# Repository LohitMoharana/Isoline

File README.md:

<p align="center">
  <b>A heartbeat classifier that sleeps through the flat parts of your ECG.</b><br>
  Two comparators, a few kilobytes of trees, and no ADC streaming in between beats.
</p>

<p align="center">

</p>

---

## 🫀 The idea

An ECG spends most of its time on the flat **isoelectric line**. Isoline does not sample it. Two comparators emit an
*up* or *down* event whenever the signal moves by 0.1 mV, so a quiet baseline produces nothing and the processor sleeps.
Each heartbeat becomes a short burst of events, which a few-kilobyte tree model turns into one of the four AAMI classes:
**N**ormal, **S**upraventricular, **V**entricular or **F**usion.

<br>

| 95.6 % | 5.2 KB | ~90 % | 0.96 |
|:--:|:--:|:--:|:--:|
| accuracy on unseen patients | the tiny classifier | of the time with no events | V-beat F1 |
| <sub>MIT-BIH inter-patient split</sub> | <sub>94.8 % with the AF detector</sub> | <sub>front end and compute stay quiet</sub> | <sub>above a clean re-run of the best published method</sub> |

<br>

## ⚙️ How it works

```mermaid
flowchart LR
    A["ECG<br/>physical mV"] --> B["Analog front end<br/>high-pass · gain · 40 Hz low-pass"]
    B --> C["Two comparators<br/>±0.1 mV level crossing"]
    C -->|sparse up / down events| D["Integer features<br/>event histograms · RR timing<br/>per-patient templates"]
    D --> E["Boosted trees<br/>5.2 KB · integer compares"]
    C -->|beat times| G["AF detector<br/>RR intervals only"]
    G -->|no S labels during AF| E
    E --> F["N · S · V · F"]
```

| Stage | What it does | Why it is cheap |
|---|---|---|
| Level crossing | two comparators and a DAC replace the ADC | about 55 events per second; nothing at all on a flat line |
| Event features | 32-bin up/down histograms around each beat, gain-normalised | counters and shifts |
| Patient adaptation | a running template and four online clusters of *this* patient's beat shapes | about 800 bytes of state, strictly causal |
| Rhythm | RR ratios over short and long memory, plus an RR-only AF/flutter detector | one timer and a few divides per beat |
| Classifier | gradient-boosted trees whose every split is an integer comparison | about 840 compares per beat |

## 📊 Results

All numbers are on **DS2**: 22 patients never seen in training, under the standard de Chazal inter-patient protocol.

<picture>
  <source media="(prefers-color-scheme: dark)" srcset="docs/img/size_vs_accuracy_dark.png">
  
</picture>

| Model | Input | Size | Accuracy | V F1 | S F1 |
|---|---|--:|--:|--:|--:|
| **Isoline, full + AF detector** | comparator events | ~55 KB | **95.64 ± 0.04 %** | **0.956** | 0.32 |
| **Isoline, tiny + AF detector** | comparator events | **5.2 + 5.1 KB** | 94.81 ± 0.04 % | 0.947 | 0.32 |
| Isoline, int8 CNN | comparator events | 9 KB | 93.7 ± 0.4 % | 0.89 | 0.17 |
| RF paper ([Saenz-Cogollo & Agelli 2020](https://doi.org/10.3390/a13040075)), our clean re-run | full-rate ECG | ~300 KB | 95.39 ± 0.09 % | 0.89 | 0.63 |
| LUT / logic-gate networks (2026 preprint) | full-rate ECG | ~16 KB (est.) | 93.6–94.4 % | ≤ 0.91 | 0.01–0.47 |
| Best reported on this split | full-rate ECG | not reported | 96.15 % | 0.94 | 0.69 |

<picture>
  <source media="(prefers-color-scheme: dark)" srcset="docs/img/per_class_dark.png">
  
</picture>

> [!NOTE]
> **Strong on ventricular beats, weak on supraventricular ones.** V beats carry the clearest morphology and need no
> P-wave. S beats that are *not* premature can only be told apart by P-wave shape. Even a full-resolution P-wave
> did not help with the little training data available for them (DS1 has 268 such beats, almost all from two
> patients), so the blind spot is a data limit, not only a front-end one.
> An optional **S-sensitive mode** raises S sensitivity from 22 % to 37 % for 0.6 points of accuracy.
> [Details](docs/EXPERIMENTS.md)

## 🔌 From simulation to silicon

The same model is carried through every stage of the hardware chain. Each stage is measured on DS2 with nothing re-tuned.

| Stage | What runs | DS2 result |
|---|---|---|
| Python front-end model | the reference pipeline (0.05 Hz high-pass, as in the circuit) | 95.51 % full · 94.76 % tiny |
| ngspice circuit | records passed through the simulated analog front end (INA333, servo, gain, Sallen-Key filter) | 95.50 % full · 94.74 % tiny |
| Firmware, virtual hardware-in-the-loop | the **unmodified STM32L432 firmware** (interrupts, DAC thresholds, streaming features, int8 trees) against simulated comparators and DAC | **93.49 % end-to-end**, missed beats counted as errors; beat detection Se 99.69 %, +P 99.08 % |
| Printed circuit board | rev A carrier for a Nucleo-L432KC, 84 × 52 mm, 2 layers, routed and DRC-clean | Gerbers ready; not yet built |

<div align="center">

<br><sub>Rev A, top side. The analog chain runs left to right into the comparators; the Nucleo-32 plugs into the two sockets on the right.</sub>
</div>

<br>

The analog front end draws about **110–170 µW** ([power budget](hardware/POWER_BUDGET.md)). The firmware fits in 66 KB of
flash and 25 KB of RAM on the STM32L432KC, and its features are **bit-exact** with the Python reference.
See [`hardware/`](hardware) for the circuit, simulation and PCB, and [`firmware/`](firmware) for the code.

## 🛡️ Robustness

<table>
<tr>
<td width="56%">
<picture>
  <source media="(prefers-color-scheme: dark)" srcset="docs/img/noise_dark.png">
  
</picture>
</td>
<td>

**Cross-database**, trained once and never tuned:

| Database | Accuracy | V Se |
|---|--:|--:|
| MIT-BIH Supraventricular | 90.3 % | 0.92 |
| European ST-T | 94.8 % | 0.85 |
| MIT-BIH Long-Term | 92.6 % | 0.90 |
| Normal Sinus Rhythm | 99.4 % | – |

Baseline wander is harmless; electrode motion below about 6 dB is the hard case. False alarms on other databases
(4–7 % of normal beats) remain the open problem.

</td>
</tr>
</table>

## 🔬 Method

<picture>
  <source media="(prefers-color-scheme: dark)" srcset="docs/img/journey_dark.png">
  
</picture>

Every configuration was chosen on DS1 or on other databases, then frozen, then evaluated on DS2. Ideas that looked good
in development and failed on unseen patients stay in the record. DS2 has been evaluated **14 times** over the project,
always with frozen configurations. That count is disclosed because it makes any comparison slightly optimistic.
The full lab notebook is [`docs/EXPERIMENTS.md`](docs/EXPERIMENTS.md); the locked configuration (model v1.0) is
described in [`docs/STATUS.md`](docs/STATUS.md).

<details>
<summary><b>Research-integrity rules</b></summary>
<br>

- DS2 is the test set. It is never used for tuning, feature choice, thresholds or early stopping.
- Splits are by **patient**. Extra databases (INCART, SVDB, AFDB, LTDB) are training or development data only.
- Inputs are in physical millivolts with no per-beat normalisation, because real comparators see real volts.
- Features are causal.
- Results are reported as mean ± std over seeds, and negative results are kept.
- Published baselines are re-run under the same protocol before any comparison.
</details>

## 🚀 Reproduce

```bash
pip install -r requirements.txt
python scripts/data/download_data.py --only mitdb svdb                                     # PhysioNet
python -m pytest -q tests                                                                  # feature logic

python scripts/final/final_af_detector.py data/mitdb data/incart data/afdb data/cache results/final   # headline
python scripts/export/export_c.py data/mitdb data/incart data/afdb data/cache                     # C export
python firmware/stm32/sim/hil_run.py data/mitdb DS2 hil.json                               # firmware in the loop
python hardware/kicad/gen/build.py                                                         # board, from netlist to Gerbers
python scripts/figures/make_readme_figures.py                                              # charts
python scripts/figures/make_hero.py --data-dir data/mitdb                                  # banner
```

## 🗂️ Repository

```
isoline/            Python package: front-end model, level crossing, integer features, pipeline
scripts/
  data/             dataset download and synthetic data
  dev/              experiments on DS1 and other databases (never DS2)
  final/            frozen evaluations on DS2 and the shared model code
  export/           C export of the trained model
  figures/          the charts in this README
export/             generated C model (isoline_model.h)
firmware/
  core/             portable C feature and streaming core, bit-exact with Python
  stm32/            STM32L432 application, linker script, Makefile; sim/ holds the virtual HIL
  test/             bit-exactness harnesses
hardware/
  design.py         component values shared by simulation and schematic
  sim/              ngspice front-end simulation
  kicad/            KiCad project; gen/ rebuilds it from design.py
  fab/              Gerbers, drill, BOM, pick-and-place, DRC report
  img/              board renders and schematic
results/
  final/            DS2 results behind every number above
  dev/              development logs
  hardware/         circuit, firmware and HIL results
  archive/          superseded runs
docs/               experiment log, project status, archive
```

## 📄 License

MIT. A research prototype, not a medical device.

<br>

<p align="center"><sub>
Why “Isoline”? The isoelectric line is the flat baseline of an ECG, the part Isoline refuses to spend energy on.
</sub></p>

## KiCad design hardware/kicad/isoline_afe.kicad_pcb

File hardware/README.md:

# Isoline hardware

Status: **design + simulation**. Nothing has been built yet.

## Analog front end (proposal) and its ngspice check

```
electrodes ─► INA333 (G=10, 50 µA) ─► ×30 gain (TLV8541) ─► 40 Hz Sallen-Key LPF (TLV8541) ─► 2 comparators ─► MCU
                 ▲ REF                                                                       (±30 mV steps)
                 └── DC servo integrator (TLV8541, 10 MΩ / 330 nF → 0.05 Hz high-pass)
```

* Total gain 300, so a 0.1 mV input step is **30 mV at the comparators**, which clears the TLV3691's ±17 mV hysteresis.
  At gain 100, a 10 mV step would be swallowed by the hysteresis. This is a design constraint the simulation-only model did not show.
* High-pass at **0.05 Hz**: the algorithm study showed that a 0.5 Hz corner distorts QRS shape and costs accuracy.
* `sim/make_afe_sim.py` writes `sim/afe.cir`, runs ngspice on a real MIT-BIH segment (record 101, with a 100 mV electrode
  offset) and compares the circuit with the Python AFE model used for every accuracy number:

| check | result |
|---|---|
| waveform correlation (input-referred, after 2 s) | **0.993** |
| RMS difference | **25 µV** (a quarter of one 0.1 mV comparator step) |
| level-crossing events, circuit vs model | **433 vs 435 (−0.5 %)** |
| output swing | 0.30 – 1.99 V on a 0–3 V supply (headroom OK) |

* **Known issue:** at power-up the 0.05 Hz servo takes several seconds to cancel electrode offset, and the gain stage
  saturates meanwhile. The simulation starts the servo pre-charged, and the board needs a fast-restore switch (the AD8233
  integrates one). That is a design to-do.
* Op amps are behavioural models (gain, GBW and rail limits from datasheets). Vendor SPICE models should replace them before tape-out.

### Classification accuracy through the simulated circuit

`sim/eval_circuit_accuracy.py` runs all 22 DS2 records through the circuit. ngspice computes the small-signal response
of the netlist and rail clipping is applied (validated against the full transient run: r = 0.99995, 439 vs 433
events). The round-10 system then classifies the result. Models are trained on DS1 + INCART with the Python AFE set to
the circuit's 0.05 Hz high-pass. Nothing is tuned; this is a measurement ([`results/hardware/circuit_accuracy.json`](../results/hardware/circuit_accuracy.json)).

| DS2, 5 seeds | Python AFE model | **ngspice circuit** |
|---|---|---|
| full model + AF detector | 95.51 ± 0.13 % | **95.50 ± 0.11 %** |
| tiny 5.2 KB + AF detector | 94.76 ± 0.11 % | **94.74 ± 0.06 %** |
| idle sparsity | 89.6 % | 89.6 % |
| output clipping | – | 0 % |

Not yet modelled: comparator offset and hysteresis, electrode noise, and beat detection from events (all accuracy
numbers here use annotated R-peak positions, as is standard on this benchmark).

See [POWER_BUDGET.md](POWER_BUDGET.md) for the power analysis and the architecture decision it raises.

## KiCad schematic

`kicad/isoline_afe.kicad_sch` is a native schematic generated by `kicad/gen/make_schematic.py` from the same circuit
description. Every pin has a wire stub and a net label, grouped in six titled blocks. **Validated:** KiCad exports a
netlist from this schematic that is identical, net for net, to the generated netlist (31 nets). Open `isoline_afe.kicad_pro`,
tidy the placement if you like, then *Tools → Update PCB from Schematic*. KiCad 8/9 will upgrade the KiCad-7-format file
on save.

## KiCad: board netlist (generated from the same `design.py` as the simulation)

`kicad/gen/make_netlist.py` → `kicad/isoline_afe.net` (56 parts, 31 nets, all footprints from the standard KiCad
libraries) and `fab/bom.csv`. The board is a **carrier for a NUCLEO-L432KC** (Cortex-M4F with an on-board
ST-LINK), so there is no QFN to hand-solder and no separate programmer to buy.

**Board:** a placed and routed layout is in `kicad/isoline_afe.kicad_pcb` (see *PCB* below). To start over from the
netlist instead: KiCad PCB Editor → *File → Import → Netlist…* → `isoline_afe.net` → *Update PCB*.

| Block | Parts | Notes |
|---|---|---|
| Power | JST-PH 2-pin (BT1) to an external 2×AAA pack with switch, JP1 power select | JP1 1-2 = battery, 2-3 = Nucleo 3V3 from USB (development) |
| Reference | 2×1 MΩ divider + TLV8542 (U4B) buffer | VREF = VCC/2 |
| Input | J1 electrodes (RA−, LL+, RL), 10 k series, 10 MΩ bias to VREF | RL to VREF through 10 k |
| HIL input | J2 + 1 µF + 100 k / 100 Ω attenuator (~1/1000), JP2/JP3 | fit JP2 + JP3 **only** when injecting MIT-BIH from a DAC/audio out |
| In-amp | INA333 (U1), RG = 11.1 k (0.1 %) → G = 10 | pinout checked: RG 1/8, IN− 2, IN+ 3, V− 4, REF 5, OUT 6, V+ 7 |
| Servo / fast restore | TLV8542 U2A integrator 10 MΩ / 330 nF; SN74LVC1G66 (U3) switch + 100 k | MCU D6 (PB1) high for ~1 s at power-up |
| Gain + LPF | U2B ×30; U4A Sallen-Key 40 Hz (100 k, 100 k, 56 n, 27 n) | total gain 300 |
| Comparators | 2 × TLV3691 (U5, U6; SC70-5): UP = AFE > TH_UP, DN = AFE < TH_DN | thresholds from DAC PA4 (A3) / PA5 (A4); events to D2 (PA12) / D3 (PB0) |
| Debug | AFE_OUT → A0 (PA0) through 1 k; 8 test points | |

**Nucleo jumper note.** On the Nucleo-32, A4/A5 share pins with D4/D5 through solder bridges, so PA5 is input-only by
default. Open the relevant bridges (SB16/SB18 per UM1956) before using PA5 as DAC output, and check the exact bridge
numbers for your board revision in UM1956.

### Layout guidance (for you in KiCad)

1. **Two zones:** analog (J1, input resistors, U1, U2, U3, U4) on one side, Nucleo headers and comparators on the other.
   Use one solid ground pour on the bottom layer and do not split it.
2. **Keep high-impedance nodes tiny:** the servo node (SERVO_IN: 10 MΩ + 330 nF) and the 10 MΩ bias resistors. Use short
   traces, no vias if possible, and keep them away from the comparator outputs and the Nucleo. Consider a guard ring tied to VREF.
3. **Symmetric input routing** from J1 to U1 pins 2/3 (equal length, side by side) for CMRR.
4. **One 100 nF decoupling capacitor per IC**, placed right at its V+ pin. Put the 10 µF bulk capacitor near JP1.
5. **Comparators next to the Nucleo header**, so the fast-edged EV_UP / EV_DN traces stay short and far from the analog zone.
6. The 330 nF servo capacitor should be a low-leakage film or C0G/X7R part (leakage sets the corner frequency).
7. Header spacing: CN3 to CN4 = 15.24 mm (600 mil). Pin 1 of both is at the end **away from** the Nucleo's USB connector; with USB pointing up (top view), CN4 (VIN…A0…D13) is the left column and CN3 (D1…D12) the right one. `make_pcb.py` checks this against KiCad's `Module:Arduino_Nano` footprint.

## PCB (rev A): placed, routed, DRC-clean

| Top | Bottom (mirrored) |
|---|---|
|  |  |

- **Board:** 84 × 52 mm, 2 layers, 1.6 mm. All SMD parts are 0805 / SOIC / VSSOP / SC-70 on the top side, with hand-soldering SC-70 pads.
- **Mechanical:** four M3 holes. The Nucleo-32 plugs into two 1×15 sockets with its USB at the top edge. Nothing is placed between the socket rows: the comparators (U5, U6) sit in their own strip just left of J4, so they can be probed and reworked with the Nucleo plugged in, and the board still works if the Nucleo is soldered flat.
- **Rules:** the fab's flat-offer profile: track 0.25 mm, clearance 0.25 mm, vias 0.9 / 0.5 mm, smallest hole 0.5 mm, 1.6 mm FR-4, one rectangular outline. The 0.65 mm-pitch parts (U1 VSSOP-8; U3, U5, U6 SC-70) have their pads trimmed to 0.39 mm wide, so the gaps are 0.26 mm while staying within TI's land pattern for 0.25–0.38 mm leads. An independent geometry check gives a smallest different-net copper gap of 0.260 mm; the drills are 0.50 / 0.75 / 1.00 / 3.20 mm.
- **Ground:** the bottom layer is a near-solid GND plane (only short cross-unders), with a GND pour on top. Every SMD GND pad has its own stitching via, plus a 5 mm lattice of stitching vias.
- **Power:** 2×AAA pack off-board on a JST-PH connector (BT1; 1 = +, 2 = −) instead of the earlier Keystone holder. Its through-hole contacts and pegs collided with the analog section and the sockets.
- **How it was made (reproducible):**
  - `kicad/gen/make_pcb.py` places the parts from `isoline_afe.net` and checks the socket orientation.
  - `kicad/gen/route_grid.py` routes it with a small A* grid router written for this board: exact copper-geometry clearances, F.Cu preferred, GND fan-out first.
  - `kicad/gen/render_pcb.py` draws the pictures.
  - KiCad 7's own DRC (`fab/drc_report.txt`) reports **0 unconnected pads and 0 clearance / hole / silkscreen / courtyard violations**. The 60 remaining "library not configured" warnings only mean the build machine had no footprint library table.
- **Fabrication files:** `fab/isoline_afe_gerbers.zip` (Gerbers + Excellon drill, upload as is), `fab/isoline_afe-pos.csv` (pick-and-place), `fab/bom.csv`.

**Honest layout review (optional hand clean-up in KiCad before ordering):**
- **Electrode traces:** E_POS / E_NEG run 30–42 mm because they also reach the HIL jumpers and attenuator at the lower left. Fine at ECG frequencies, but shorter is better against mains pickup.
- **AFE_OUT** fans out to the comparators, C11, R18 and TP4 over about 70 mm with 10 vias. It is a low-impedance op-amp output, so this is harmless but untidy.
- **Servo node:** SERVO_IN (10 MΩ / 330 nF) is short (16.5 mm) with no vias. A VREF guard ring around it would further reduce leakage, but it is not drawn.
- **Decoupling:** capacitors sit 3–5 mm from their ICs rather than at the V+ pin. At these bandwidths (TLV8542 GBW 8 kHz) with a solid ground plane this is acceptable.

### Before ordering a PCB: checklist

- [ ] Re-check every footprint against the exact ordered part (package suffix: INA333AIDGK, TLV8542ID, TLV3691IDCK, SN74LVC1G66DCK).
- [ ] Confirm the Nucleo-32 header order and solder bridges in UM1956 for your board revision. Physically: hold your Nucleo with USB up, components facing you; the column with VIN/A0/D13 must land on J4 (left).
- [ ] Open the Nucleo solder bridges that tie A4/A5 to D4/D5 (SB16/SB18 per UM1956) so PA5 can drive TH_DN.
- [ ] Check the polarity of your 2×AAA pack's JST-PH lead (red to pin 1 "+"). JST lead colours are not standardised.
- [ ] Open `kicad/isoline_afe.kicad_pcb` in your KiCad, run *Inspect → Design Rules Checker* with your library table, and look at the 3D view.
- [ ] Replace the behavioural op-amp models with TI's SPICE models and re-run `sim/make_afe_sim.py`.
- [ ] Simulate the fast-restore start-up (switch on 1 s, then off).

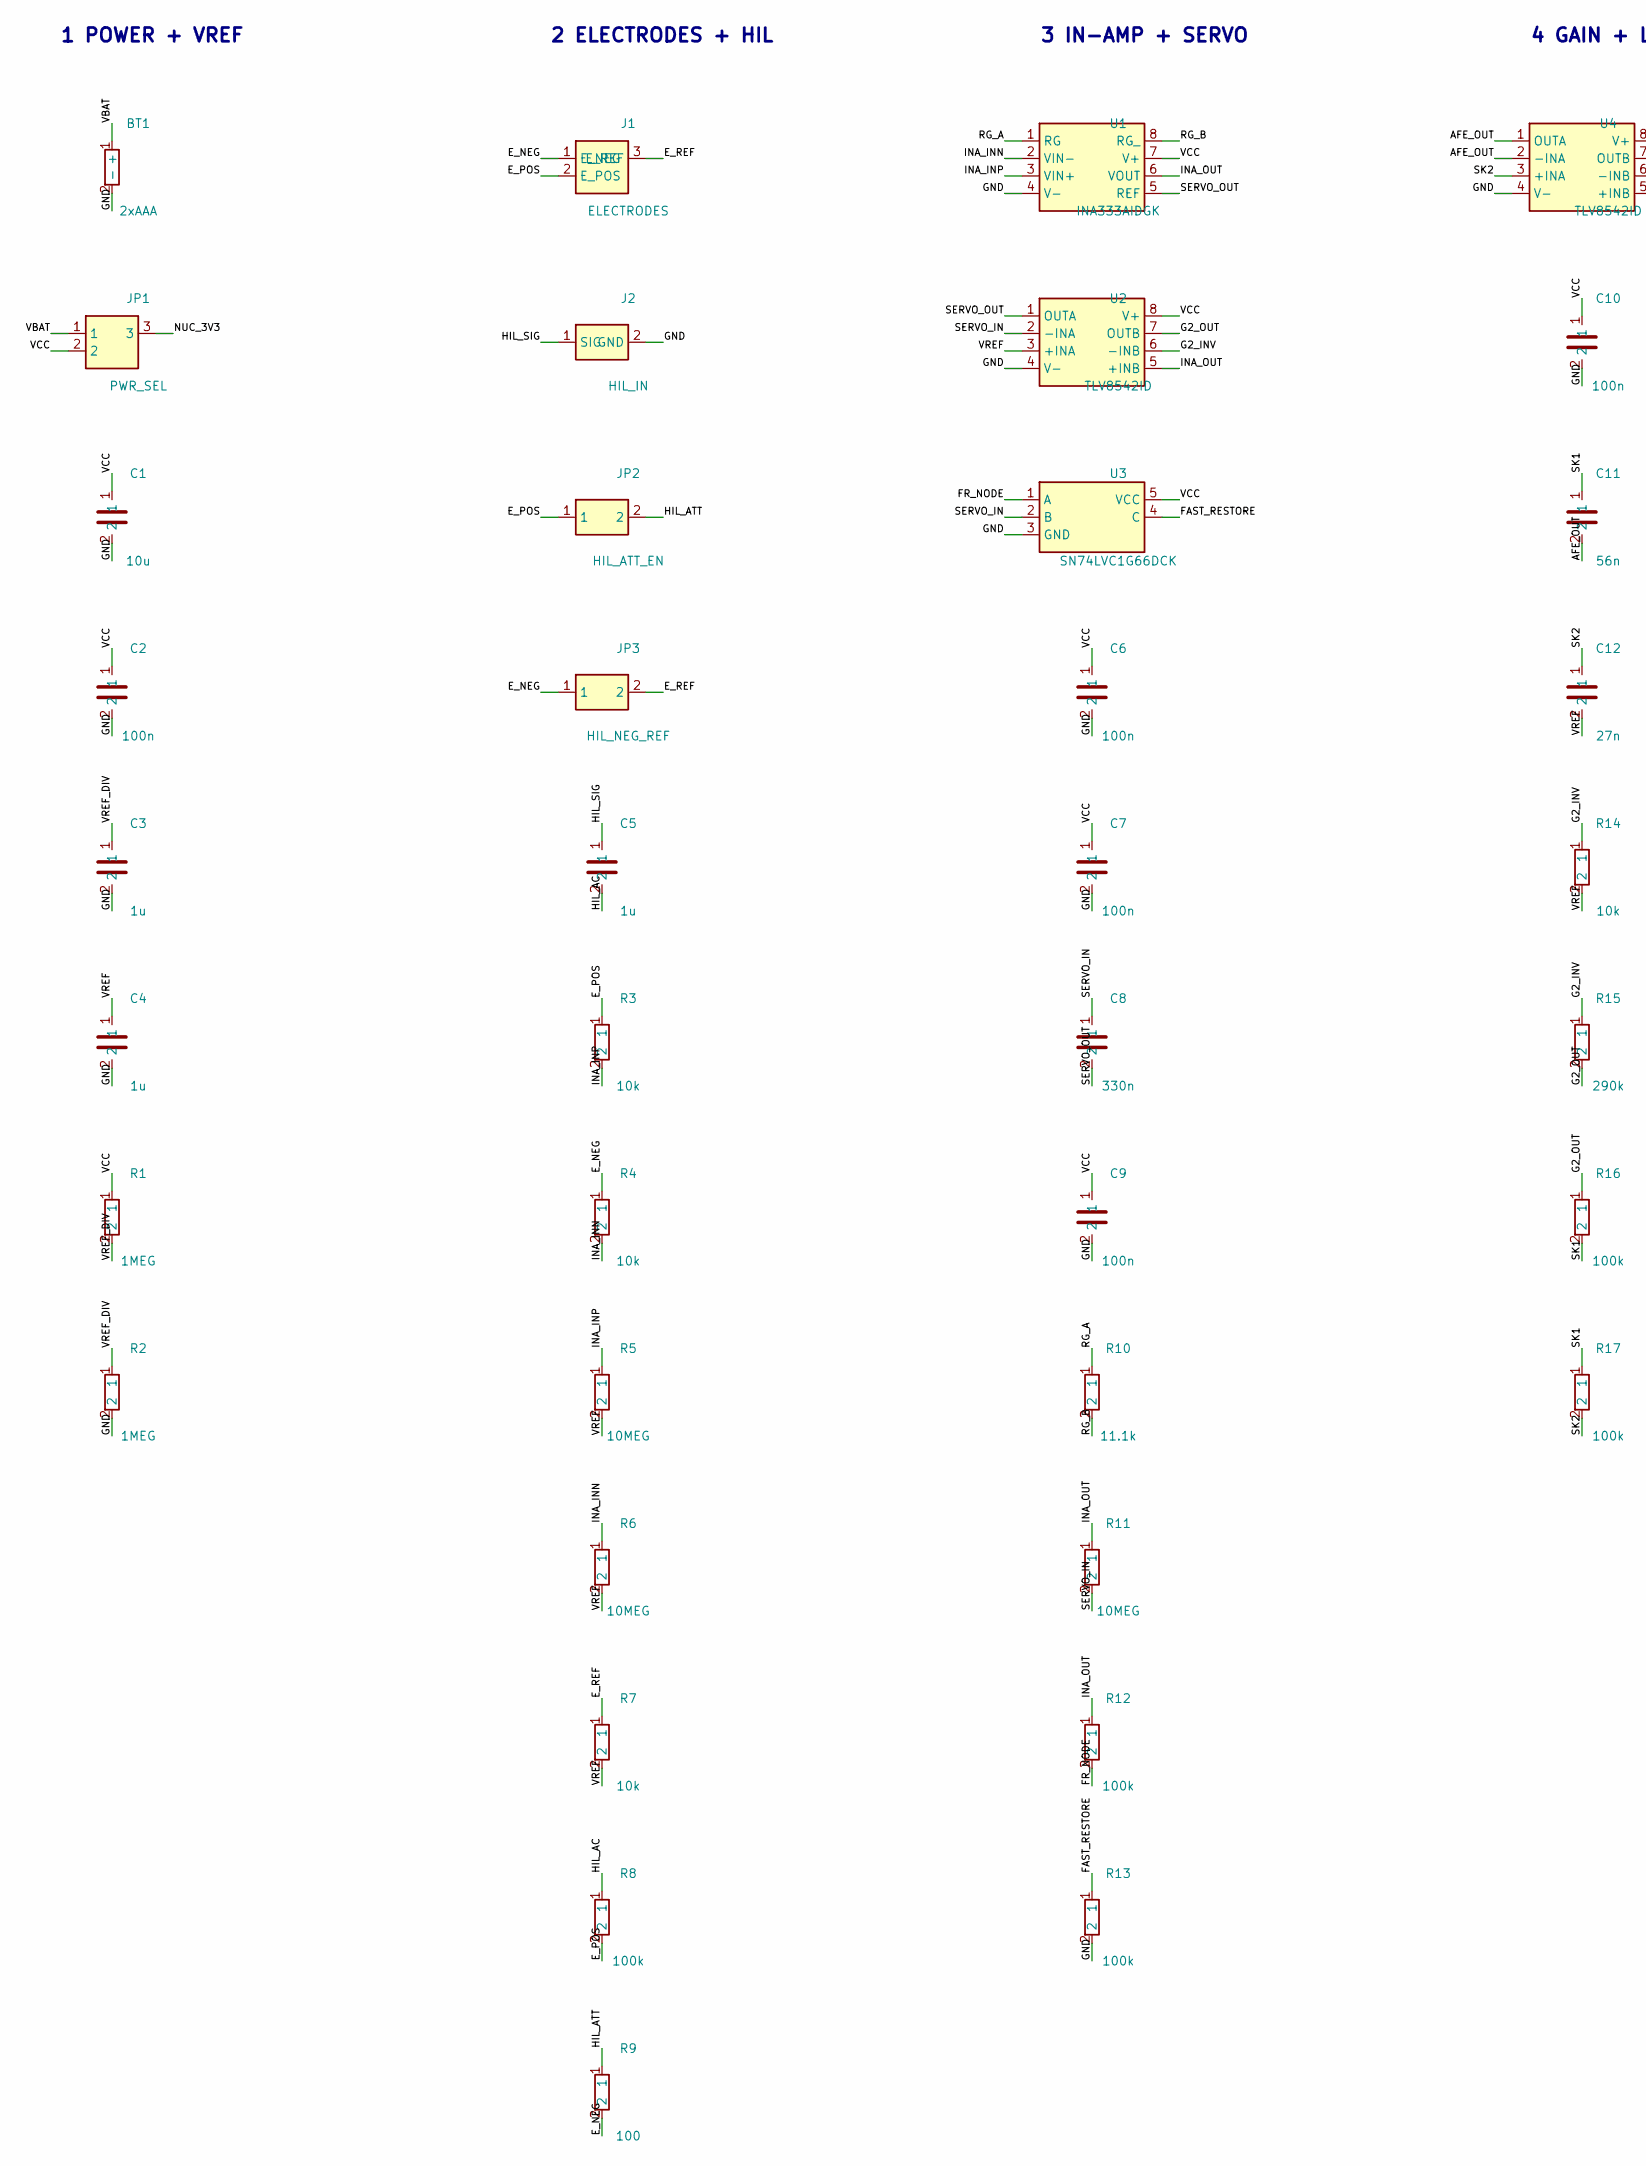
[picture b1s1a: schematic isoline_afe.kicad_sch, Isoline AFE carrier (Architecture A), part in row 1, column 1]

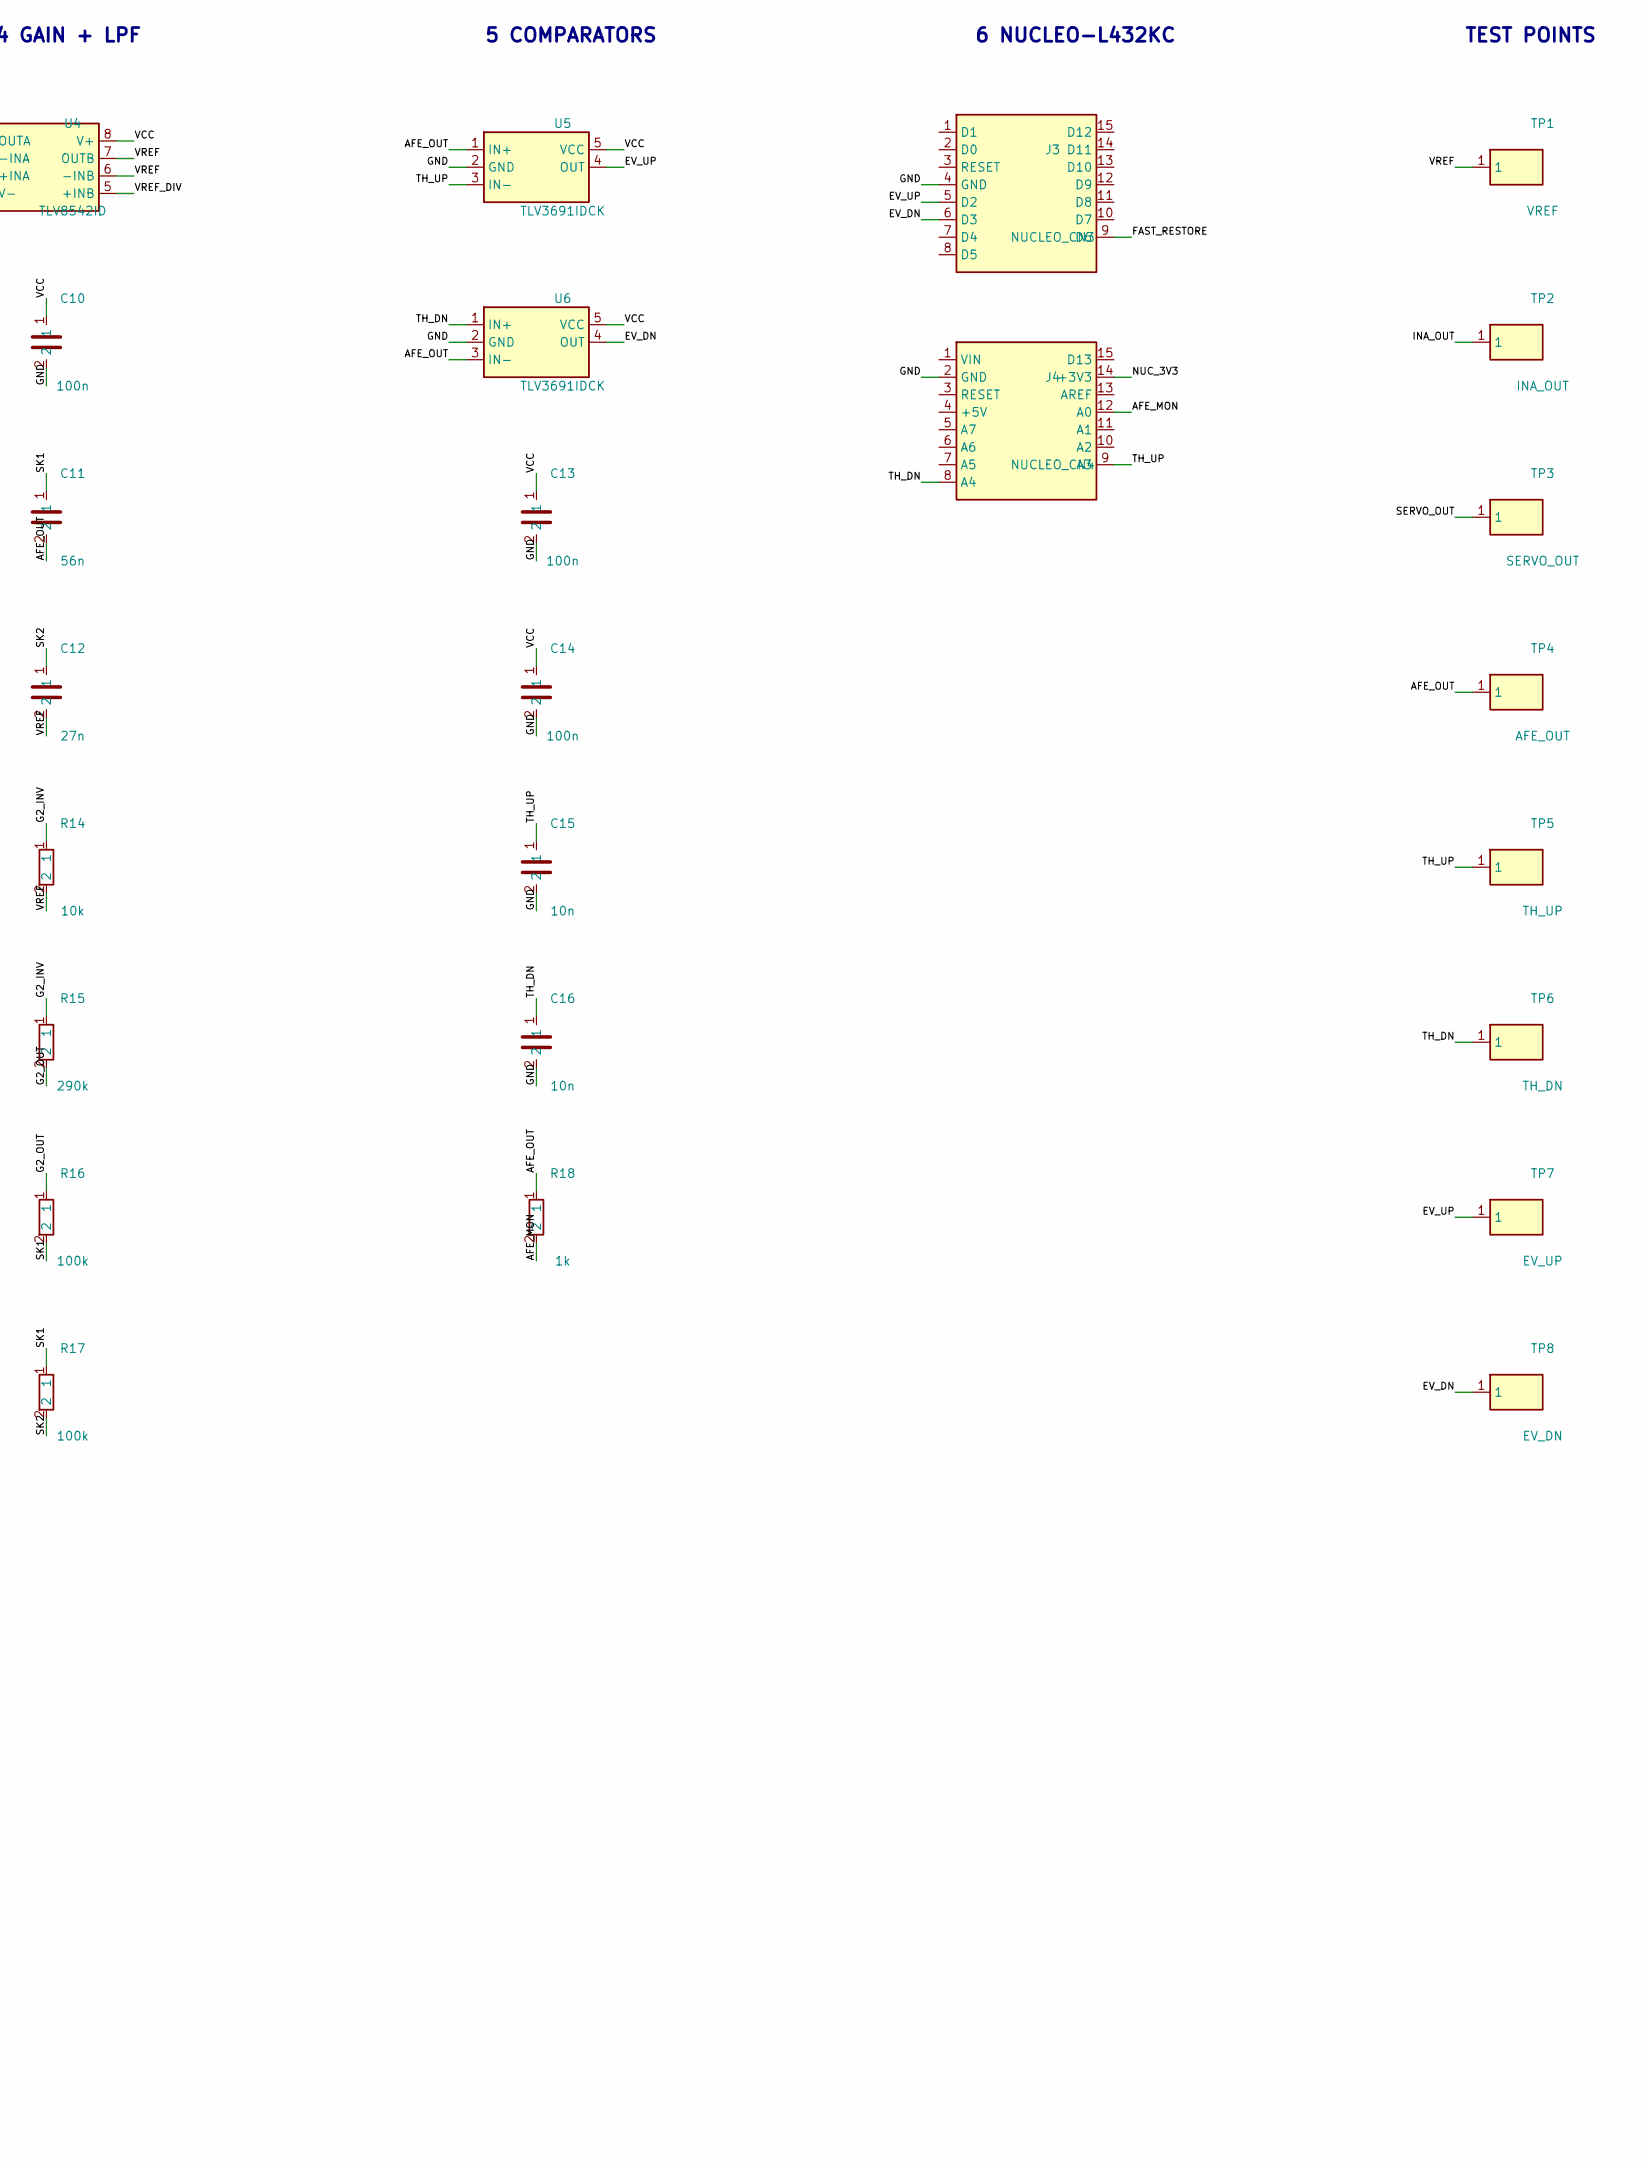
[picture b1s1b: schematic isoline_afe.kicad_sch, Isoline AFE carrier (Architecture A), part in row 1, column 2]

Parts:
BT1: 2xAAA; JST_PH_B2B-PH-K_1x02_P2.00mm_Vertical
C1: 10u; C_0805_2012Metric
C2, C6, C7, C9, C10, C13, C14: 100n; C_0805_2012Metric
C3, C4, C5: 1u; C_0805_2012Metric
C8: 330n; C_0805_2012Metric
C11: 56n; C_0805_2012Metric
C12: 27n; C_0805_2012Metric
C15, C16: 10n; C_0805_2012Metric
J1: ELECTRODES; PinHeader_1x03_P2.54mm_Vertical
J2: HIL_IN; PinHeader_1x02_P2.54mm_Vertical
J3: NUCLEO_CN3; PinSocket_1x15_P2.54mm_Vertical
J4: NUCLEO_CN4; PinSocket_1x15_P2.54mm_Vertical
JP1: PWR_SEL; PinHeader_1x03_P2.54mm_Vertical
JP2: HIL_ATT_EN; PinHeader_1x02_P2.54mm_Vertical
JP3: HIL_NEG_REF; PinHeader_1x02_P2.54mm_Vertical
R1, R2: 1MEG; R_0805_2012Metric
R3, R4, R7, R14: 10k; R_0805_2012Metric
R5, R6, R11: 10MEG; R_0805_2012Metric
R8, R12, R13, R16, R17: 100k; R_0805_2012Metric
R9: 100; R_0805_2012Metric
R10: 11.1k; R_0805_2012Metric
R15: 290k; R_0805_2012Metric
R18: 1k; R_0805_2012Metric
TP1: VREF; TestPoint_Pad_D1.5mm
TP2: INA_OUT; TestPoint_Pad_D1.5mm
TP3: SERVO_OUT; TestPoint_Pad_D1.5mm
TP4: AFE_OUT; TestPoint_Pad_D1.5mm
TP5: TH_UP; TestPoint_Pad_D1.5mm
TP6: TH_DN; TestPoint_Pad_D1.5mm
TP7: EV_UP; TestPoint_Pad_D1.5mm
TP8: EV_DN; TestPoint_Pad_D1.5mm
U1: INA333AIDGK; VSSOP-8_3.0x3.0mm_P0.65mm
U2, U4: TLV8542ID; SOIC-8_3.9x4.9mm_P1.27mm
U3: SN74LVC1G66DCK; SOT-353_SC-70-5_Handsoldering
U5, U6: TLV3691IDCK; SOT-353_SC-70-5_Handsoldering

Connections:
AFE_MON: J4.12 (A0), R18.2
AFE_OUT: C11.2, R18.1, TP4.1, U4.1 (OUTA), U4.2 (-INA), U5.1 (IN+), U6.3 (IN-)
EV_DN: J3.6 (D3), TP8.1, U6.4 (OUT)
EV_UP: J3.5 (D2), TP7.1, U5.4 (OUT)
E_NEG: J1.1 (E_NEG), JP3.1, R4.1, R9.2
E_POS: J1.2 (E_POS), JP2.1, R3.1, R8.2
E_REF: J1.3 (E_REF), JP3.2, R7.1
FAST_RESTORE: J3.9 (D6), R13.1, U3.4 (C)
FR_NODE: R12.2, U3.1 (A)
G2_INV: R14.1, R15.1, U2.6 (-INB)
G2_OUT: R15.2, R16.1, U2.7 (OUTB)
GND: BT1.2 (-), C1.2, C2.2, C3.2, C4.2, C6.2, C7.2, C9.2, C10.2, C13.2, C14.2, C15.2, C16.2, J2.2 (GND), J3.4 (GND), J4.2 (GND), R2.2, R13.2, U1.4 (V-), U2.4 (V-), U3.3 (GND), U4.4 (V-), U5.2 (GND), U6.2 (GND)
HIL_AC: C5.2, R8.1
HIL_ATT: JP2.2, R9.1
HIL_SIG: C5.1, J2.1 (SIG)
INA_INN: R4.2, R6.1, U1.2 (VIN-)
INA_INP: R3.2, R5.1, U1.3 (VIN+)
INA_OUT: R11.1, R12.1, TP2.1, U1.6 (VOUT), U2.5 (+INB)
NUC_3V3: J4.14 (+3V3), JP1.3
RG_A: R10.1, U1.1 (RG)
RG_B: R10.2, U1.8 (RG_)
SERVO_IN: C8.1, R11.2, U2.2 (-INA), U3.2 (B)
SERVO_OUT: C8.2, TP3.1, U1.5 (REF), U2.1 (OUTA)
SK1: C11.1, R16.2, R17.1
SK2: C12.1, R17.2, U4.3 (+INA)
TH_DN: C16.1, J4.8 (A4), TP6.1, U6.1 (IN+)
TH_UP: C15.1, J4.9 (A3), TP5.1, U5.3 (IN-)
VBAT: BT1.1 (+), JP1.1
VCC: C1.1, C2.1, C6.1, C7.1, C9.1, C10.1, C13.1, C14.1, JP1.2, R1.1, U1.7 (V+), U2.8 (V+), U3.5 (VCC), U4.8 (V+), U5.5 (VCC), U6.5 (VCC)
VREF: C4.1, C12.2, R5.2, R6.2, R7.2, R14.2, TP1.1, U2.3 (+INA), U4.6 (-INB), U4.7 (OUTB)
VREF_DIV: C3.1, R1.2, R2.1, U4.5 (+INB)

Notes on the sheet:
1 POWER + VREF
2 ELECTRODES + HIL
3 IN-AMP + SERVO
4 GAIN + LPF
5 COMPARATORS
6 NUCLEO-L432KC
TEST POINTS

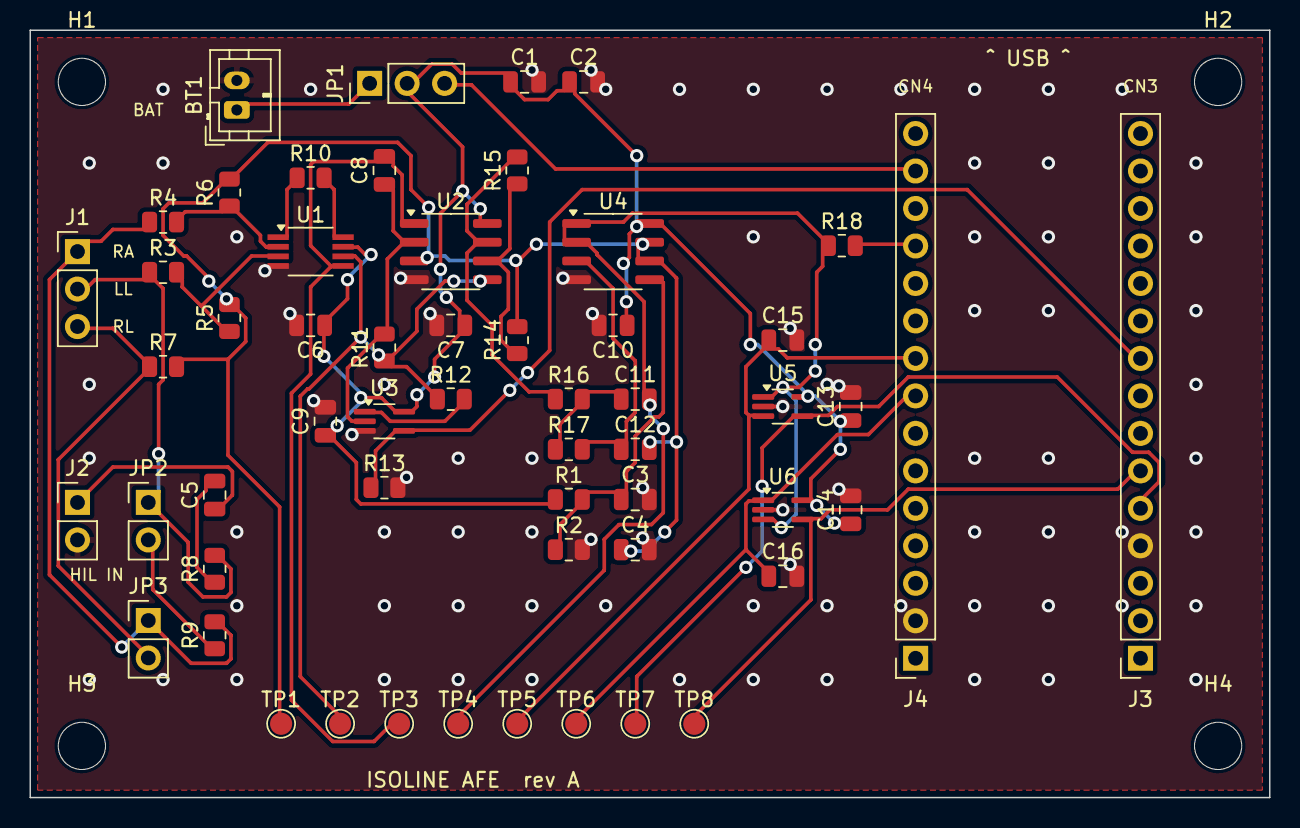
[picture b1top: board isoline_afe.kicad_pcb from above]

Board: 2 copper layers, 84.0 x 52.0 mm, 60 parts (0 on the bottom side), 31 nets.

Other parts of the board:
H1, H2, H3, H4: M3; MountingHole_3.2mm_M3

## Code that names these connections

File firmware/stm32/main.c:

/* Isoline application for the NUCLEO-L432KC on the Isoline AFE carrier board (hardware/kicad).
 * Register-level (CMSIS only, no HAL). Pin map (hardware/kicad/gen/make_netlist.py):
 *   PA4  DAC1_OUT1 -> TH_UP  (upper comparator threshold)      PA12 <- EV_UP  (TLV3691 #1 output, EXTI12)
 *   PA5  DAC1_OUT2 -> TH_DN  (lower comparator threshold)      PB0  <- EV_DN  (TLV3691 #2 output, EXTI0)
 *   PB1  -> FAST_RESTORE (servo fast-restore switch)            PA2  -> USART2_TX (ST-LINK virtual COM port)
 * Timebase: LPTIM1 clocked from LSE 32.768 kHz, period 91 -> 360.09 Hz slot tick (= the 360 Hz model timebase).
 *
 * Level crossing (matches isoline.afe): the DAC holds ref +/- step. A rising edge on EV_UP means the AFE output
 * crossed ref + step: count one up event and move both thresholds up by one step. Steep QRS edges can cross several
 * steps inside one slot; the comparator output then stays high, so each slot tick also re-checks the outputs and keeps
 * stepping (with a settle delay for the TLV3691's 24 us response) while they are still asserted.
 *
 * TODO (documented in firmware/README.md): Stop 2 instead of Sleep between slots (DAC sample-and-hold), VDDA
 * tracking of the DAC step via VREFINT, event-timestamp mode without the periodic tick.
 */
#include <stdint.h>
#include "stm32l432xx.h"
#include "isoline_stream.h"
#include "isoline_model.h"

#define DAC_STEP 41u            /* 30 mV at VDDA = 3.0 V: 0.1 mV input x gain 300 (hardware/design.py) */
#define DAC_MID 2048u           /* VREF = VDDA / 2 */
#define SETTLE_LOOPS 40         /* ~30 us at 4 MHz: TLV3691 response time is 24 us */
#define MAX_STEPS_PER_SLOT 16

static volatile uint16_t ev_up, ev_dn;          /* events in the current slot (ISR -> tick) */
static volatile int32_t ref_code = DAC_MID;
static volatile uint8_t slot_ready;
static volatile uint16_t slot_up, slot_dn;
static iso_stream S;

static void dac_write(void) {
    int32_t up = ref_code + DAC_STEP, dn = ref_code - DAC_STEP;
    if (up > 4095) up = 4095;
    if (dn < 0) dn = 0;
    DAC1->DHR12R1 = (uint32_t)up;
    DAC1->DHR12R2 = (uint32_t)dn;
}

static inline int ev_up_level(void) { return (GPIOA->IDR >> 12) & 1u; }
static inline int ev_dn_level(void) { return (GPIOB->IDR >> 0) & 1u; }
#ifdef ISO_HOST_SIM   /* virtual-HIL build (sim/hil_sim.c): the simulator stands in for analog time and the UART */
static void settle(void) { sim_settle(); }
#else
static void settle(void) { for (volatile int i = 0; i < SETTLE_LOOPS; i++) { } }
#endif

void EXTI15_10_IRQHandler(void) {                /* EV_UP rising edge */
    if (EXTI->PR1 & EXTI_PR1_PIF12) { EXTI->PR1 = EXTI_PR1_PIF12; ev_up++; ref_code += DAC_STEP; dac_write(); }
}

void EXTI0_IRQHandler(void) {                    /* EV_DN rising edge */
    if (EXTI->PR1 & EXTI_PR1_PIF0) { EXTI->PR1 = EXTI_PR1_PIF0; ev_dn++; ref_code -= DAC_STEP; dac_write(); }
}

void LPTIM1_IRQHandler(void) {                   /* 360 Hz slot boundary */
    if (LPTIM1->ISR & LPTIM_ISR_ARRM) {
        LPTIM1->ICR = LPTIM_ICR_ARRMCF;
        for (int k = 0; k < MAX_STEPS_PER_SLOT; k++) {   /* steep edges: comparators still asserted -> more steps */
            settle();
            if (ev_up_level()) { ev_up++; ref_code += DAC_STEP; dac_write(); }
            else if (ev_dn_level()) { ev_dn++; ref_code -= DAC_STEP; dac_write(); }
            else break;
        }
        slot_up = ev_up; slot_dn = ev_dn; ev_up = 0; ev_dn = 0; slot_ready = 1;
    }
}

static void uart_init(void) {                    /* USART2 on PA2 (AF7), 115200 baud from MSI 4 MHz */
    RCC->APB1ENR1 |= RCC_APB1ENR1_USART2EN;
    GPIOA->MODER = (GPIOA->MODER & ~(3u << 4)) | (2u << 4);
    GPIOA->AFR[0] = (GPIOA->AFR[0] & ~(0xFu << 8)) | (7u << 8);
    USART2->BRR = 4000000u / 115200u;
    USART2->CR1 = USART_CR1_TE | USART_CR1_UE;
}

static void uart_puts(const char *s) {
#ifdef ISO_HOST_SIM
    while (*s) sim_uart_putc(*s++);
#else
    while (*s) { while (!(USART2->ISR & USART_ISR_TXE)) { } USART2->TDR = (uint8_t)*s++; }
#endif
}

static void uart_putu(uint32_t v) {
    char b[11]; int i = 10; b[i] = 0;
    do { b[--i] = (char)('0' + v % 10u); v /= 10u; } while (v);
    uart_puts(&b[i]);
}

static void hw_init(void) {
    RCC->AHB2ENR |= RCC_AHB2ENR_GPIOAEN | RCC_AHB2ENR_GPIOBEN;
    RCC->APB1ENR1 |= RCC_APB1ENR1_DAC1EN | RCC_APB1ENR1_LPTIM1EN | RCC_APB1ENR1_PWREN;
    RCC->APB2ENR |= RCC_APB2ENR_SYSCFGEN;
    /* analog mode on PA4/PA5 (DAC outputs) - reset default is analog on L4; make it explicit */
    GPIOA->MODER |= (3u << 8) | (3u << 10);
    /* PA12, PB0 inputs (comparator outputs are push-pull, no pull needed) */
    GPIOA->MODER &= ~(3u << 24);
    GPIOB->MODER &= ~(3u << 0);
    /* PB1 output: fast-restore switch */
    GPIOB->MODER = (GPIOB->MODER & ~(3u << 2)) | (1u << 2);
    /* DAC: both channels, buffer on */
    DAC1->CR = DAC_CR_EN1 | DAC_CR_EN2;
    dac_write();
    /* EXTI12 <- PA12, EXTI0 <- PB0, rising edges */
    SYSCFG->EXTICR[3] = (SYSCFG->EXTICR[3] & ~SYSCFG_EXTICR4_EXTI12) | SYSCFG_EXTICR4_EXTI12_PA;
    SYSCFG->EXTICR[0] = (SYSCFG->EXTICR[0] & ~SYSCFG_EXTICR1_EXTI0) | SYSCFG_EXTICR1_EXTI0_PB;
    EXTI->RTSR1 |= EXTI_RTSR1_RT12 | EXTI_RTSR1_RT0;
    EXTI->IMR1 |= EXTI_IMR1_IM12 | EXTI_IMR1_IM0;
    NVIC_EnableIRQ(EXTI15_10_IRQn); NVIC_EnableIRQ(EXTI0_IRQn);
    /* LSE on (Nucleo-L432KC fits a 32.768 kHz crystal; verify for your board revision) */
    PWR->CR1 |= PWR_CR1_DBP;
    RCC->BDCR |= RCC_BDCR_LSEON;
    while (!(RCC->BDCR & RCC_BDCR_LSERDY)) { }
    RCC->CCIPR = (RCC->CCIPR & ~RCC_CCIPR_LPTIM1SEL) | (3u << RCC_CCIPR_LPTIM1SEL_Pos);   /* LPTIM1 clock = LSE */
    LPTIM1->IER = LPTIM_IER_ARRMIE;
    LPTIM1->CR = LPTIM_CR_ENABLE;
    LPTIM1->ARR = 90;                                   /* 91 LSE ticks = 2.777 ms = 360.09 Hz */
    LPTIM1->CR |= LPTIM_CR_CNTSTRT;
    NVIC_EnableIRQ(LPTIM1_IRQn);
}

#ifdef ISO_HOST_SIM
static void delay_ms(uint32_t ms) { (void)ms; }     /* fast restore is not part of the steady-state AFE model */
#else
static void delay_ms(uint32_t ms) { for (volatile uint32_t i = 0; i < ms * 500u; i++) { } }
#endif

int main(void) {
    hw_init();
    uart_init();
    GPIOB->BSRR = 1u << 1; delay_ms(1000); GPIOB->BRR = 1u << 1;    /* fast-restore the 0.05 Hz servo for 1 s */
    iso_stream_init(&S);
    uart_puts("isoline ready\r\n");
    static const char cls[4] = {'N', 'S', 'V', 'F'};
    iso_beat out[2];
    for (;;) {
        __WFI();                                         /* Sleep until the next interrupt */
        if (!slot_ready) continue;
        slot_ready = 0;
        int n = iso_stream_push(&S, slot_up, slot_dn, out, 2);
        for (int i = 0; i < n; i++) {
            if (out[i].have_feat != 1) continue;
            int c = isoline_classify(out[i].feat, out[i].af_valid ? out[i].af : 0, 1);
            char tail[4] = {' ', cls[c], '\r', 0};
            uart_putu((uint32_t)out[i].r); uart_puts(tail); uart_puts("\n");
        }
    }
}

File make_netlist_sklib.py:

from collections import defaultdict
from skidl import Pin, Part, Alias, SchLib, SKIDL, TEMPLATE

from skidl.pin import pin_types

SKIDL_lib_version = '0.0.1'

make_netlist = SchLib(tool=SKIDL).add_parts(*[
        Part(**{ 'name':'Battery_2xAAA', 'dest':TEMPLATE, 'tool':SKIDL, 'aliases':Alias({'Battery_2xAAA'}), 'ref_prefix':'BT', 'fplist':None, 'footprint':'Battery:BatteryHolder_Keystone_2468_2xAAA', 'keywords':None, 'description':'', 'datasheet':None, 'pins':[
            Pin(num='1',name='+',func=pin_types.UNSPEC),
            Pin(num='2',name='-',func=pin_types.UNSPEC)] }),
        Part(**{ 'name':'Jumper_3', 'dest':TEMPLATE, 'tool':SKIDL, 'aliases':Alias({'Jumper_3'}), 'ref_prefix':'JP', 'fplist':None, 'footprint':'Connector_PinHeader_2.54mm:PinHeader_1x03_P2.54mm_Vertical', 'keywords':None, 'description':'', 'datasheet':None, 'pins':[
            Pin(num='1',name='1',func=pin_types.UNSPEC),
            Pin(num='2',name='2',func=pin_types.UNSPEC),
            Pin(num='3',name='3',func=pin_types.UNSPEC)] }),
        Part(**{ 'name':'C', 'dest':TEMPLATE, 'tool':SKIDL, 'aliases':Alias({'C'}), 'ref_prefix':'C', 'fplist':None, 'footprint':'Capacitor_SMD:C_0805_2012Metric', 'keywords':None, 'description':'', 'datasheet':None, 'pins':[
            Pin(num='1',name='1',func=pin_types.UNSPEC),
            Pin(num='2',name='2',func=pin_types.UNSPEC)] }),
        Part(**{ 'name':'R', 'dest':TEMPLATE, 'tool':SKIDL, 'aliases':Alias({'R'}), 'ref_prefix':'R', 'fplist':None, 'footprint':'Resistor_SMD:R_0805_2012Metric', 'keywords':None, 'description':'', 'datasheet':None, 'pins':[
            Pin(num='1',name='1',func=pin_types.UNSPEC),
            Pin(num='2',name='2',func=pin_types.UNSPEC)] }),
        Part(**{ 'name':'Conn_Electrodes', 'dest':TEMPLATE, 'tool':SKIDL, 'aliases':Alias({'Conn_Electrodes'}), 'ref_prefix':'J', 'fplist':None, 'footprint':'Connector_PinHeader_2.54mm:PinHeader_1x03_P2.54mm_Vertical', 'keywords':None, 'description':'', 'datasheet':None, 'pins':[
            Pin(num='1',name='E_NEG',func=pin_types.UNSPEC),
            Pin(num='2',name='E_POS',func=pin_types.UNSPEC),
            Pin(num='3',name='E_REF',func=pin_types.UNSPEC)] }),
        Part(**{ 'name':'Conn_HIL', 'dest':TEMPLATE, 'tool':SKIDL, 'aliases':Alias({'Conn_HIL'}), 'ref_prefix':'J', 'fplist':None, 'footprint':'Connector_PinHeader_2.54mm:PinHeader_1x02_P2.54mm_Vertical', 'keywords':None, 'description':'', 'datasheet':None, 'pins':[
            Pin(num='1',name='SIG',func=pin_types.UNSPEC),
            Pin(num='2',name='GND',func=pin_types.UNSPEC)] }),
        Part(**{ 'name':'Jumper_2', 'dest':TEMPLATE, 'tool':SKIDL, 'aliases':Alias({'Jumper_2'}), 'ref_prefix':'JP', 'fplist':None, 'footprint':'Connector_PinHeader_2.54mm:PinHeader_1x02_P2.54mm_Vertical', 'keywords':None, 'description':'', 'datasheet':None, 'pins':[
            Pin(num='1',name='1',func=pin_types.UNSPEC),
            Pin(num='2',name='2',func=pin_types.UNSPEC)] }),
        Part(**{ 'name':'INA333', 'dest':TEMPLATE, 'tool':SKIDL, 'aliases':Alias({'INA333'}), 'ref_prefix':'U', 'fplist':None, 'footprint':'Package_SO:VSSOP-8_3x3mm_P0.65mm', 'keywords':None, 'description':'', 'datasheet':None, 'pins':[
            Pin(num='1',name='RG',func=pin_types.UNSPEC),
            Pin(num='2',name='VIN-',func=pin_types.UNSPEC),
            Pin(num='3',name='VIN+',func=pin_types.UNSPEC),
            Pin(num='4',name='V-',func=pin_types.UNSPEC),
            Pin(num='5',name='REF',func=pin_types.UNSPEC),
            Pin(num='6',name='VOUT',func=pin_types.UNSPEC),
            Pin(num='7',name='V+',func=pin_types.UNSPEC),
            Pin(num='8',name='RG_',func=pin_types.UNSPEC)] }),
        Part(**{ 'name':'TLV8542', 'dest':TEMPLATE, 'tool':SKIDL, 'aliases':Alias({'TLV8542'}), 'ref_prefix':'U', 'fplist':None, 'footprint':'Package_SO:SOIC-8_3.9x4.9mm_P1.27mm', 'keywords':None, 'description':'', 'datasheet':None, 'pins':[
            Pin(num='1',name='OUTA',func=pin_types.UNSPEC),
            Pin(num='2',name='-INA',func=pin_types.UNSPEC),
            Pin(num='3',name='+INA',func=pin_types.UNSPEC),
            Pin(num='4',name='V-',func=pin_types.UNSPEC),
            Pin(num='5',name='+INB',func=pin_types.UNSPEC),
            Pin(num='6',name='-INB',func=pin_types.UNSPEC),
            Pin(num='7',name='OUTB',func=pin_types.UNSPEC),
            Pin(num='8',name='V+',func=pin_types.UNSPEC)] }),
        Part(**{ 'name':'SN74LVC1G66', 'dest':TEMPLATE, 'tool':SKIDL, 'aliases':Alias({'SN74LVC1G66'}), 'ref_prefix':'U', 'fplist':None, 'footprint':'Package_TO_SOT_SMD:SOT-353_SC-70-5', 'keywords':None, 'description':'', 'datasheet':None, 'pins':[
            Pin(num='1',name='A',func=pin_types.UNSPEC),
            Pin(num='2',name='B',func=pin_types.UNSPEC),
            Pin(num='3',name='GND',func=pin_types.UNSPEC),
            Pin(num='4',name='C',func=pin_types.UNSPEC),
            Pin(num='5',name='VCC',func=pin_types.UNSPEC)] }),
        Part(**{ 'name':'TLV3691', 'dest':TEMPLATE, 'tool':SKIDL, 'aliases':Alias({'TLV3691'}), 'ref_prefix':'U', 'fplist':None, 'footprint':'Package_TO_SOT_SMD:SOT-353_SC-70-5', 'keywords':None, 'description':'', 'datasheet':None, 'pins':[
            Pin(num='1',name='IN+',func=pin_types.UNSPEC),
            Pin(num='2',name='GND',func=pin_types.UNSPEC),
            Pin(num='3',name='IN-',func=pin_types.UNSPEC),
            Pin(num='4',name='OUT',func=pin_types.UNSPEC),
            Pin(num='5',name='VCC',func=pin_types.UNSPEC)] }),
        Part(**{ 'name':'Nucleo32_CN3', 'dest':TEMPLATE, 'tool':SKIDL, 'aliases':Alias({'Nucleo32_CN3'}), 'ref_prefix':'J', 'fplist':None, 'footprint':'Connector_PinSocket_2.54mm:PinSocket_1x15_P2.54mm_Vertical', 'keywords':None, 'description':'', 'datasheet':None, 'pins':[
            Pin(num='1',name='D1',func=pin_types.UNSPEC),
            Pin(num='2',name='D0',func=pin_types.UNSPEC),
            Pin(num='3',name='RESET',func=pin_types.UNSPEC),
            Pin(num='4',name='GND',func=pin_types.UNSPEC),
            Pin(num='5',name='D2',func=pin_types.UNSPEC),
            Pin(num='6',name='D3',func=pin_types.UNSPEC),
            Pin(num='7',name='D4',func=pin_types.UNSPEC),
            Pin(num='8',name='D5',func=pin_types.UNSPEC),
            Pin(num='9',name='D6',func=pin_types.UNSPEC),
            Pin(num='10',name='D7',func=pin_types.UNSPEC),
            Pin(num='11',name='D8',func=pin_types.UNSPEC),
            Pin(num='12',name='D9',func=pin_types.UNSPEC),
            Pin(num='13',name='D10',func=pin_types.UNSPEC),
            Pin(num='14',name='D11',func=pin_types.UNSPEC),
            Pin(num='15',name='D12',func=pin_types.UNSPEC)] }),
        Part(**{ 'name':'Nucleo32_CN4', 'dest':TEMPLATE, 'tool':SKIDL, 'aliases':Alias({'Nucleo32_CN4'}), 'ref_prefix':'J', 'fplist':None, 'footprint':'Connector_PinSocket_2.54mm:PinSocket_1x15_P2.54mm_Vertical', 'keywords':None, 'description':'', 'datasheet':None, 'pins':[
            Pin(num='1',name='VIN',func=pin_types.UNSPEC),
            Pin(num='2',name='GND',func=pin_types.UNSPEC),
            Pin(num='3',name='RESET',func=pin_types.UNSPEC),
            Pin(num='4',name='+5V',func=pin_types.UNSPEC),
            Pin(num='5',name='A7',func=pin_types.UNSPEC),
            Pin(num='6',name='A6',func=pin_types.UNSPEC),
            Pin(num='7',name='A5',func=pin_types.UNSPEC),
            Pin(num='8',name='A4',func=pin_types.UNSPEC),
            Pin(num='9',name='A3',func=pin_types.UNSPEC),
            Pin(num='10',name='A2',func=pin_types.UNSPEC),
            Pin(num='11',name='A1',func=pin_types.UNSPEC),
            Pin(num='12',name='A0',func=pin_types.UNSPEC),
            Pin(num='13',name='AREF',func=pin_types.UNSPEC),
            Pin(num='14',name='+3V3',func=pin_types.UNSPEC),
            Pin(num='15',name='D13',func=pin_types.UNSPEC)] }),
        Part(**{ 'name':'TestPoint', 'dest':TEMPLATE, 'tool':SKIDL, 'aliases':Alias({'TestPoint'}), 'ref_prefix':'TP', 'fplist':None, 'footprint':'TestPoint:TestPoint_Pad_D1.5mm', 'keywords':None, 'description':'', 'datasheet':None, 'pins':[
            Pin(num='1',name='1',func=pin_types.UNSPEC)] })])

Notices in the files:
README.md:
MIT license
